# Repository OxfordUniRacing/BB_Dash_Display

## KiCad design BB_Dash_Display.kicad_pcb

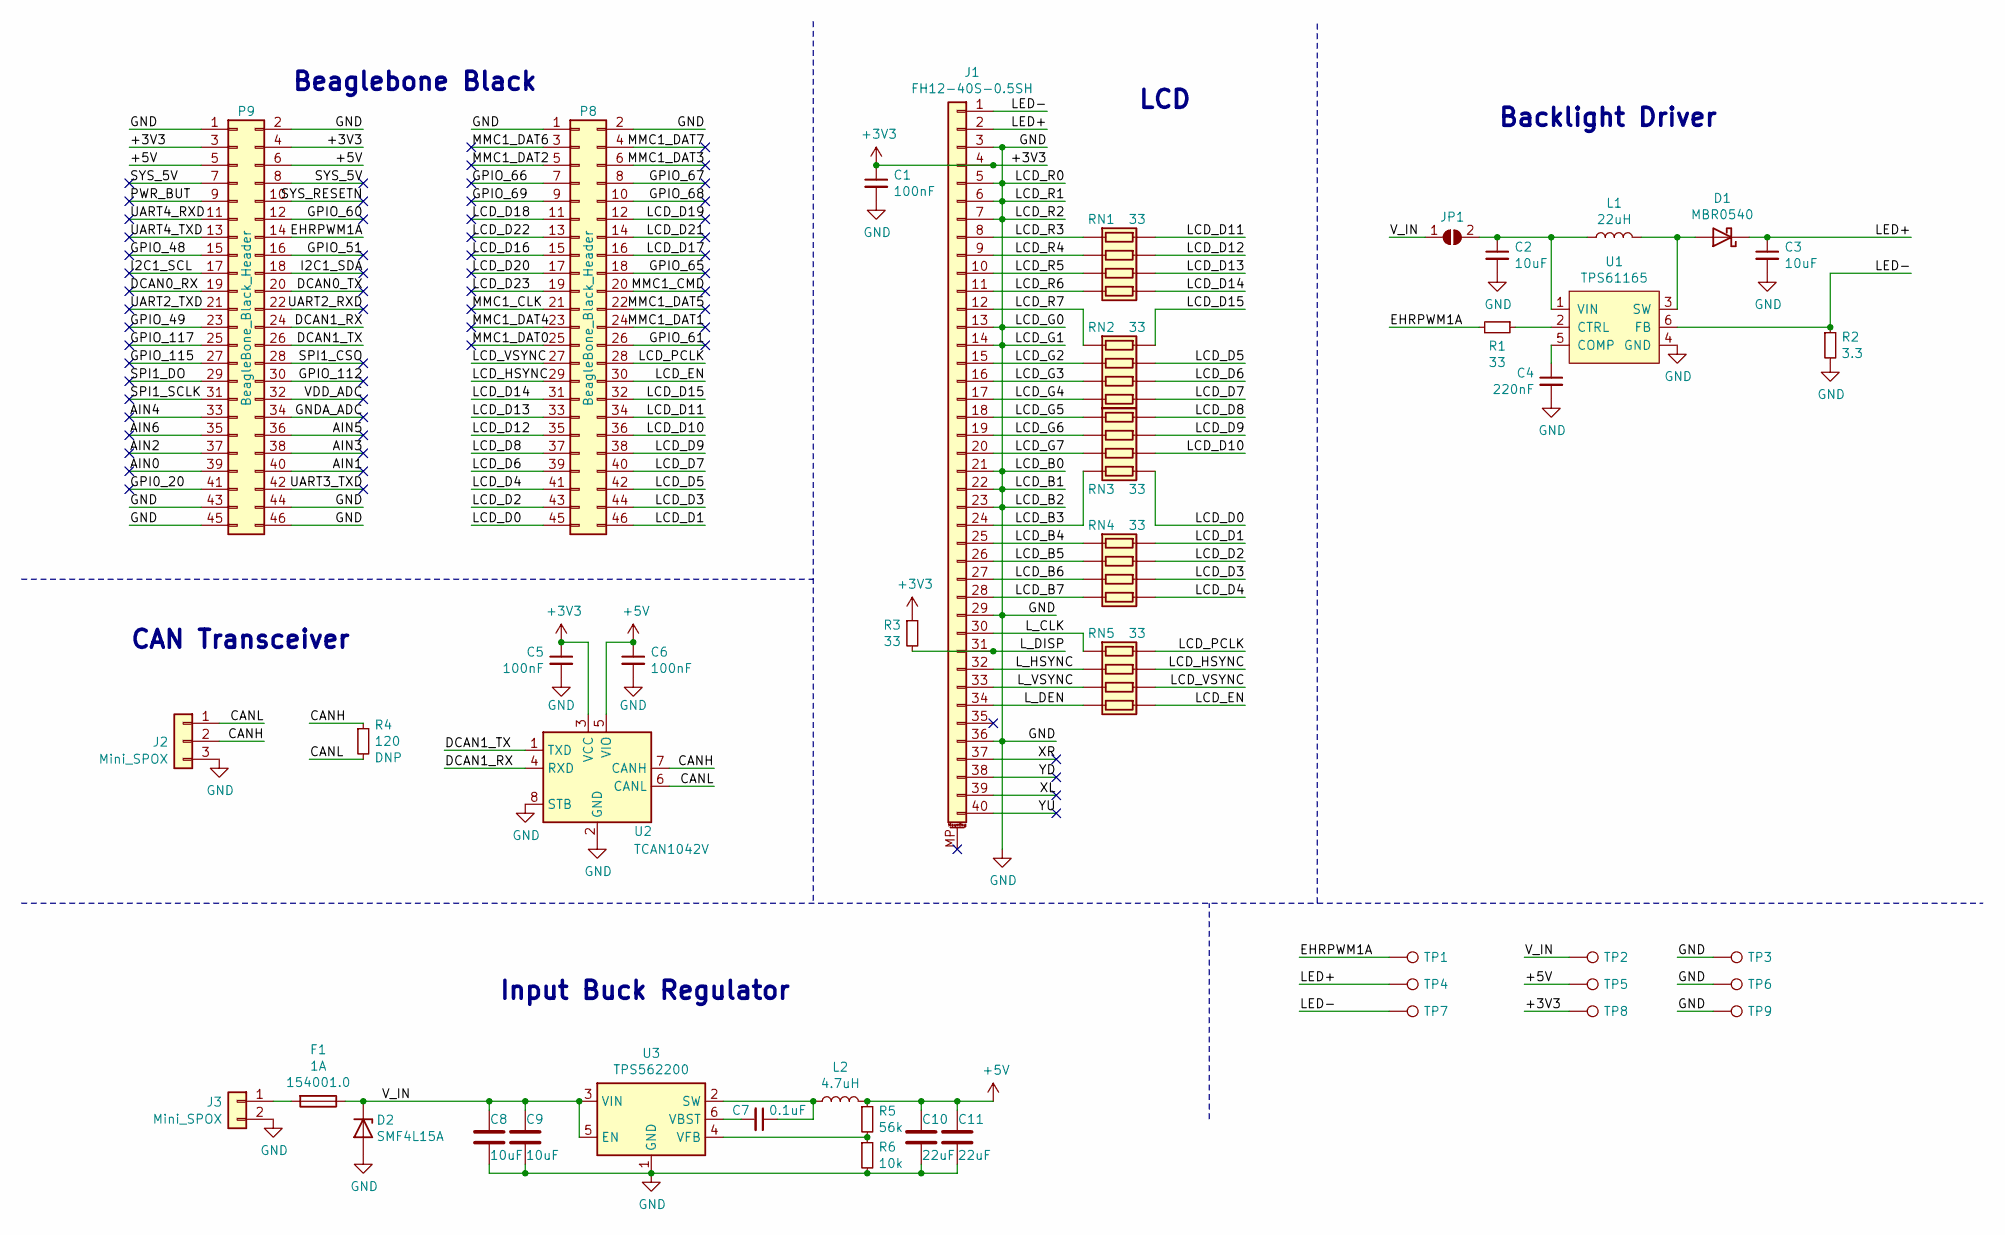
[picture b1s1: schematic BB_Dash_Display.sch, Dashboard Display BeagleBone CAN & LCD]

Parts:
C1, C5, C6: 100nF; C_0805_2012Metric
C2: 10uF; C_1206_3216Metric; Voltage 25V
C3: 10uF; C_1210_3225Metric
C4: 220nF; C_0805_2012Metric
C7: 0.1uF; C_0805_2012Metric
C8, C9: 10uF; C_1206_3216Metric
C10, C11: 22uF; C_0805_2012Metric
D1: MBR0540; D_SOD-123; Part MBR0540
D2: SMF4L15A; D_SOD-123; Part SMF4L15A
F1: 1A; Fuseholder_Littelfuse_Nano2_154x; Part 154001.0
J1: FH12-40S-0.5SH; Hirose_FH12-40S-0.5SH_1x40-1MP_P0.50mm_Horizontal; Part FH12-40S-0.5SH
J2: Mini_SPOX; Molex_SPOX_5268-03A_1x03_P2.50mm_Horizontal; Part 22057035
J3: Mini_SPOX; Molex_SPOX_5268-02A_1x02_P2.50mm_Horizontal; Part 22057025
JP1: SolderJumper_2_Open; SolderJumper-2_P1.3mm_Open_TrianglePad1.0x1.5mm
L1: 22uH; L_Bourns-SRN4018; Part SRN4018-220M
L2: 4.7uH; L_Bourns-SRN4018; Part SRN4018-4R7M
P8, P9: BeagleBone_Black_Header; PinHeader_2x23_P2.54mm_Vertical_Flip
R1, R3: 33; R_0805_2012Metric
R2: 3.3; R_0805_2012Metric
R4: 120; R_0805_2012Metric; Part 120Ω 0805
R5: 56k; R_0805_2012Metric
R6: 10k; R_0805_2012Metric
RN1, RN2, RN3, RN4, RN5: 33; R_Array_Convex_4x0603; Part YC164-JR-0733RL
TP1, TP2, TP3, TP4, TP5, TP6, TP7, TP8, TP9: TestPoint; TestPoint_THTPad_D2.0mm_Drill1.0mm
U1: TPS61165; SOT-23-6; Part TPS61165DBV
U2: TCAN1042V; SOIC-8_3.9x4.9mm_P1.27mm; Part TCAN1042V
U3: TPS562200; SOT-23-6; Part TPS562200DDC

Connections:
+3V3: C1.1, C5.1, J1.4, P9.3, P9.4, R3.1, TP8.1, U2.3 (VCC)
+5V: C6.1, C10.1, C11.1, L2.2, P9.5, P9.6, R5.1, TP5.1, U2.5 (VIO)
/AIN0: P9.39
/AIN1: P9.40
/AIN2: P9.37
/AIN3: P9.38
/AIN4: P9.33
/AIN5: P9.36
/AIN6: P9.35
/CANH: J2.2, R4.1, U2.7 (CANH)
/CANL: J2.1, R4.2, U2.6 (CANL)
/DCAN0_RX: P9.19
/DCAN0_TX: P9.20
/DCAN1_RX: P9.24, U2.4 (RXD)
/DCAN1_TX: P9.26, U2.1 (TXD)
/EHRPWM1A: P9.14, R1.2, TP1.1
/GNDA_ADC: P9.34
/GPI0_20: P9.41
/GPIO_48: P9.15
/GPIO_49: P9.23
/GPIO_51: P9.16
/GPIO_60: P9.12
/GPIO_61: P8.26
/GPIO_65: P8.18
/GPIO_66: P8.7
/GPIO_67: P8.8
/GPIO_68: P8.10
/GPIO_69: P8.9
/GPIO_112: P9.30
/GPIO_115: P9.27
/GPIO_117: P9.25
/I2C1_SCL: P9.17
/I2C1_SDA: P9.18
/LCD_B3: J1.24, RN3.4 (R4.1)
/LCD_B4: J1.25, RN4.1 (R1.1)
/LCD_B5: J1.26, RN4.2 (R2.1)
/LCD_B6: J1.27, RN4.3 (R3.1)
/LCD_B7: J1.28, RN4.4 (R4.1)
/LCD_D0: P8.45, RN3.5 (R4.2)
/LCD_D1: P8.46, RN4.8 (R1.2)
/LCD_D2: P8.43, RN4.7 (R2.2)
/LCD_D3: P8.44, RN4.6 (R3.2)
/LCD_D4: P8.41, RN4.5 (R4.2)
/LCD_D5: P8.42, RN2.7 (R2.2)
/LCD_D6: P8.39, RN2.6 (R3.2)
/LCD_D7: P8.40, RN2.5 (R4.2)
/LCD_D8: P8.37, RN3.8 (R1.2)
/LCD_D9: P8.38, RN3.7 (R2.2)
/LCD_D10: P8.36, RN3.6 (R3.2)
/LCD_D11: P8.34, RN1.8 (R1.2)
/LCD_D12: P8.35, RN1.7 (R2.2)
/LCD_D13: P8.33, RN1.6 (R3.2)
/LCD_D14: P8.31, RN1.5 (R4.2)
/LCD_D15: P8.32, RN2.8 (R1.2)
/LCD_D16: P8.15
/LCD_D17: P8.16
/LCD_D18: P8.11
/LCD_D19: P8.12
/LCD_D20: P8.17
/LCD_D21: P8.14
/LCD_D22: P8.13
/LCD_D23: P8.19
/LCD_EN: P8.30, RN5.5 (R4.2)
/LCD_G2: J1.15, RN2.2 (R2.1)
/LCD_G3: J1.16, RN2.3 (R3.1)
/LCD_G4: J1.17, RN2.4 (R4.1)
/LCD_G5: J1.18, RN3.1 (R1.1)
/LCD_G6: J1.19, RN3.2 (R2.1)
/LCD_G7: J1.20, RN3.3 (R3.1)
/LCD_HSYNC: P8.29, RN5.7 (R2.2)
/LCD_PCLK: P8.28, RN5.8 (R1.2)
/LCD_R3: J1.8, RN1.1 (R1.1)
/LCD_R4: J1.9, RN1.2 (R2.1)
/LCD_R5: J1.10, RN1.3 (R3.1)
/LCD_R6: J1.11, RN1.4 (R4.1)
/LCD_R7: J1.12, RN2.1 (R1.1)
/LCD_VSYNC: P8.27, RN5.6 (R3.2)
/LED+: C3.1, D1.1 (K), J1.2, TP4.1
/LED-: J1.1, R2.1, TP7.1, U1.6 (FB)
/L_CLK: J1.30, RN5.1 (R1.1)
/L_DEN: J1.34, RN5.4 (R4.1)
/L_DISP: J1.31, R3.2
/L_HSYNC: J1.32, RN5.2 (R2.1)
/L_VSYNC: J1.33, RN5.3 (R3.1)
/MMC1_CLK: P8.21
/MMC1_CMD: P8.20
/MMC1_DAT0: P8.25
/MMC1_DAT1: P8.24
/MMC1_DAT2: P8.5
/MMC1_DAT3: P8.6
/MMC1_DAT4: P8.23
/MMC1_DAT5: P8.22
/MMC1_DAT6: P8.3
/MMC1_DAT7: P8.4
/PWR_BUT: P9.9
/SPI1_CSO: P9.28
/SPI1_DO: P9.29
/SPI1_SCLK: P9.31
/SYS_5V: P9.7, P9.8
/SYS_RESETN: P9.10
/UART2_RXD: P9.22
/UART2_TXD: P9.21
/UART3_TXD: P9.42
/UART4_RXD: P9.11
/UART4_TXD: P9.13
/VDD_ADC: P9.32
/V_IN: C8.1, C9.1, D2.1 (K), F1.1, JP1.1 (A), TP2.1, U3.3 (VIN), U3.5 (EN)
/XL: J1.39
/XR: J1.37
/YD: J1.38
/YU: J1.40
GND: C1.2, C2.2, C3.2, C4.2, C5.2, C6.2, C8.2, C9.2, C10.2, C11.2, D2.2 (A), J1.3, J1.5, J1.6, J1.7, J1.13, J1.14, J1.21, J1.22, J1.23, J1.29, J1.36, J2.3, J3.2, P8.1, P8.2, P9.1, P9.2, P9.43, P9.44, P9.45, P9.46, R2.2, R6.2, TP3.1, TP6.1, TP9.1, U1.4 (GND), U2.2 (GND), U2.8 (STB), U3.1 (GND)
unnamed: C2.1, JP1.2 (B), L1.1, U1.1 (VIN)
unnamed: C4.1, U1.5 (COMP)
unnamed: C7.1, L2.1, U3.2 (SW)
unnamed: C7.2, U3.6 (VBST)
unnamed: D1.2 (A), L1.2, U1.3 (SW)
unnamed: F1.2, J3.1
unnamed: R1.1, U1.2 (CTRL)
unnamed: R5.2, R6.1, U3.4 (VFB)

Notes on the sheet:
Beaglebone Black
LCD
Input Buck Regulator
Backlight Driver
CAN Transceiver

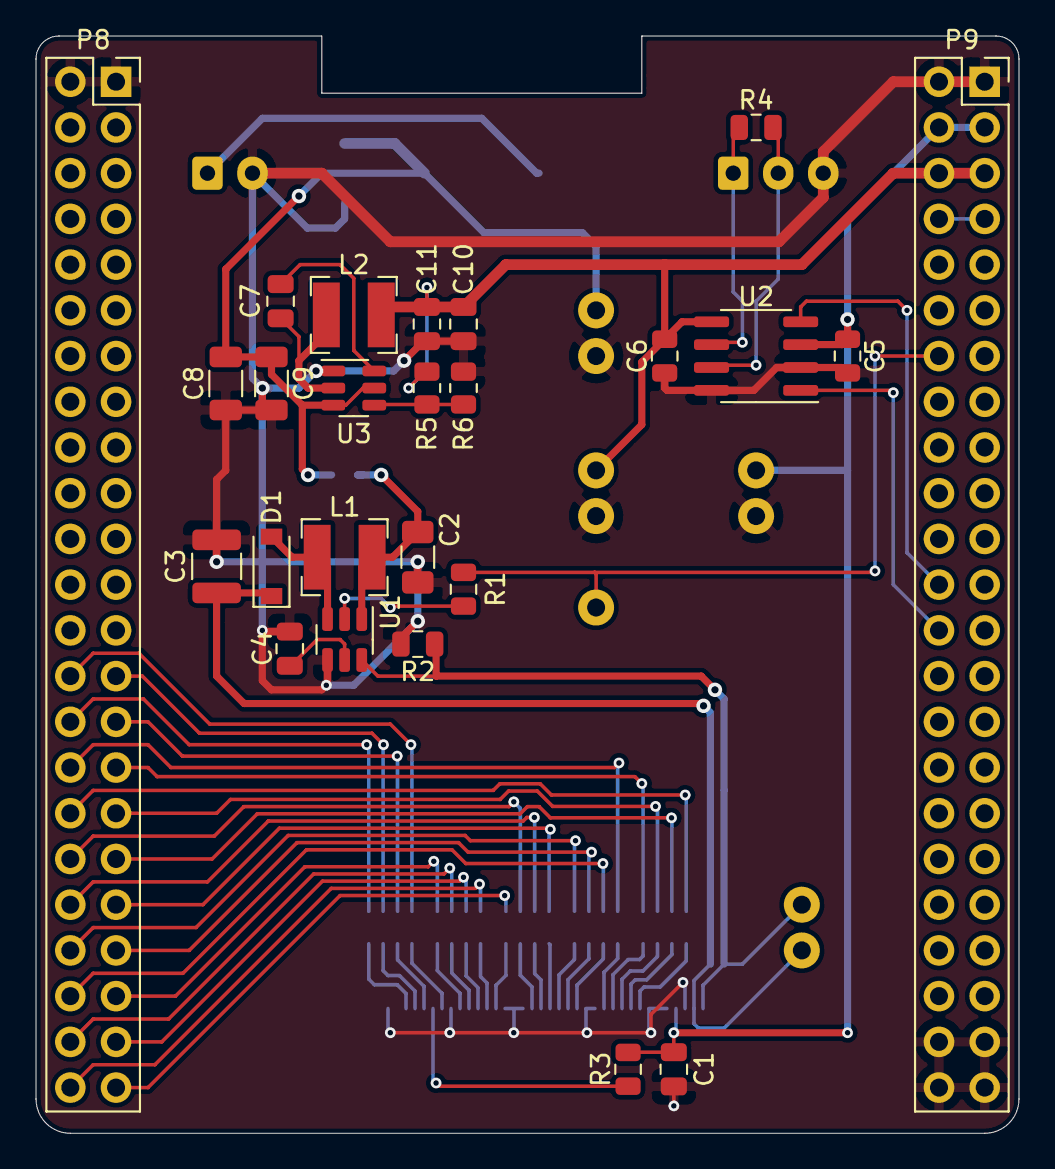
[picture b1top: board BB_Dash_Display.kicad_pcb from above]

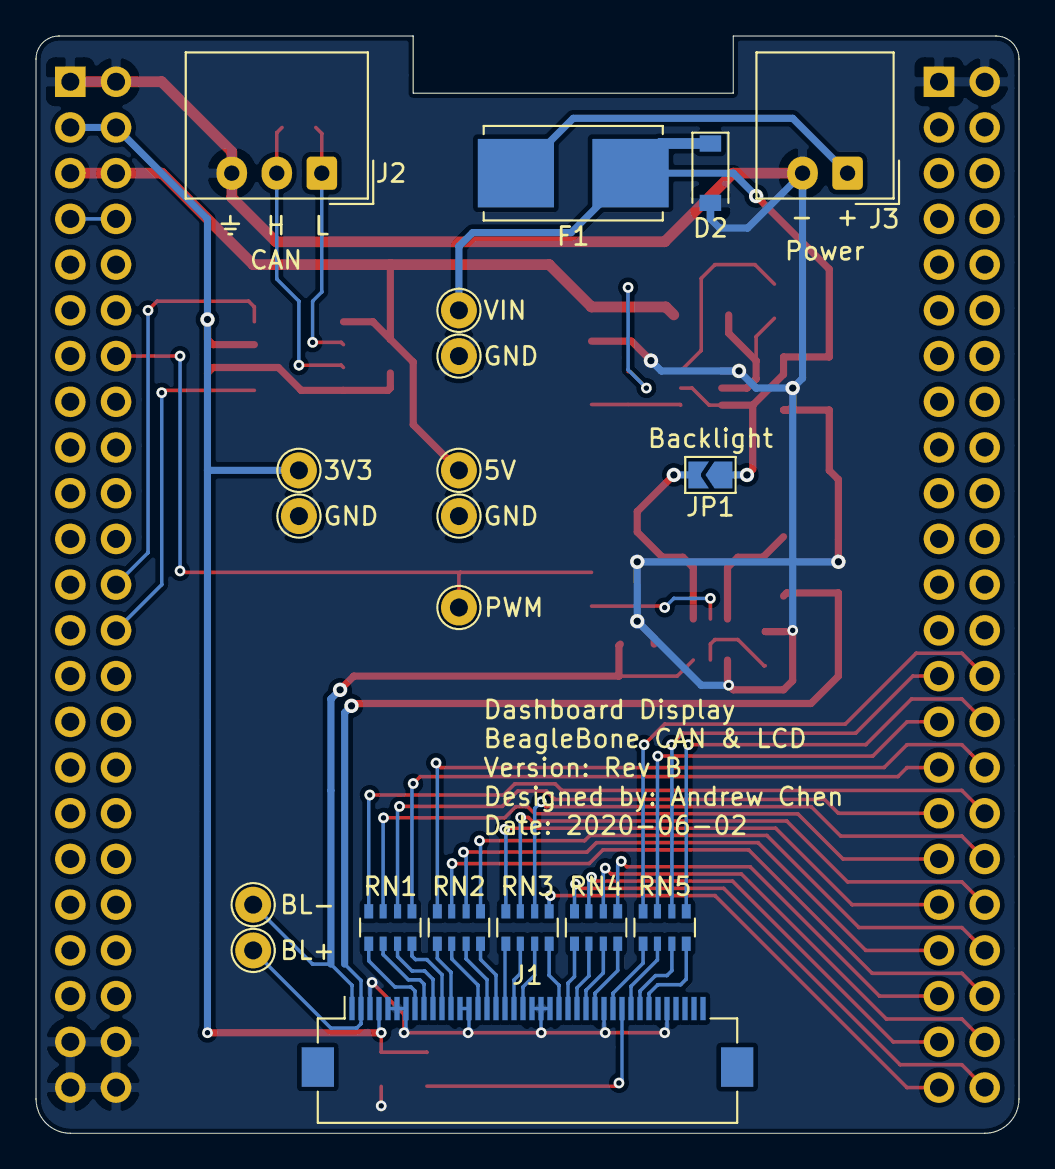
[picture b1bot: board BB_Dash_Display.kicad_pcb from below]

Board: 2 copper layers, 54.6 x 61.0 mm, 45 parts (20 on the bottom side), 61 nets.

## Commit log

2020-03-06 rev a
2020-03-07 rev a2
    Add jumper for can termination
2020-03-07 rev a3
    change to convex resistor arrays
2021-03-20 update schematics for rev b
2021-03-24 archive stuff
2021-06-02 rev b
